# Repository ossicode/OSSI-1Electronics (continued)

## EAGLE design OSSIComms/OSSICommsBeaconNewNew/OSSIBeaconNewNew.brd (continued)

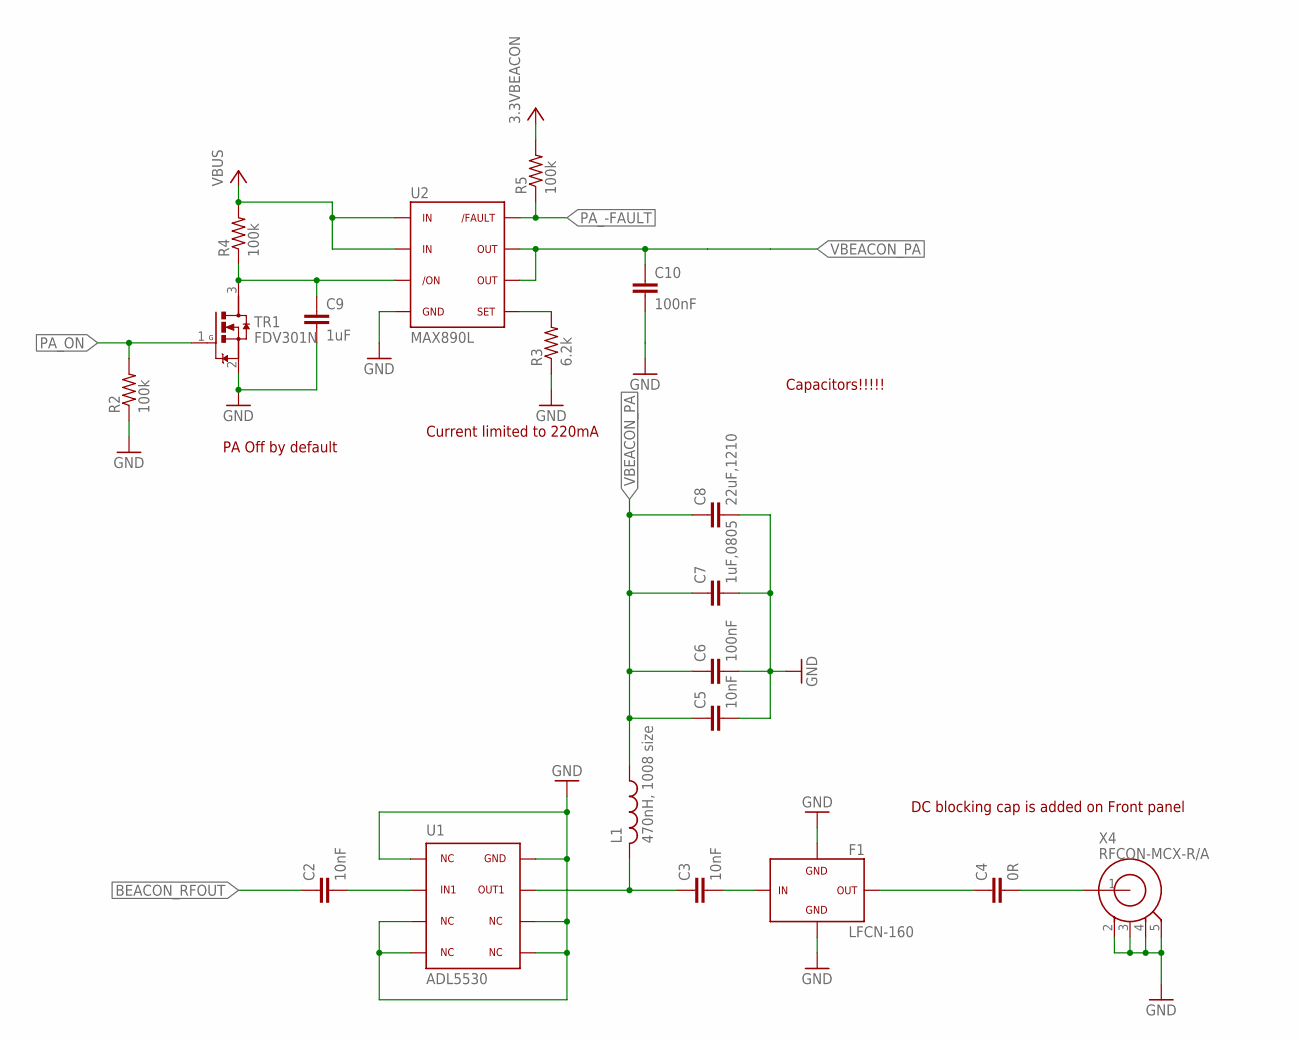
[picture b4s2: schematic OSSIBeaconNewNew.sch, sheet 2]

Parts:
C2, C3, C5: 10nF; C0603(1608)
C4: 0R; C0603(1608)
C6, C10: 100nF; C0603(1608)
C7: 1uF,0805; C0805(2012)
C8: 22uF,1210; C1210-GCM32
C9: 1uF; C0603(1608)
F1: LFCN-160; LFCN
L1: 470nH, 1008 size; L1008(2520)
R2, R4, R5: 100k; R0603(1608)
R3: 6.2k; R0603(1608)
TR1: FDV301N; SOT23
U1: ADL5530; LFCSP8_CP
U2: MAX890L; SO8
X4: RFCON-MCX-R/A; MCX-R/A

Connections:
3.3VBEACON: R5.2; also elsewhere on the board
BEACON_RFOUT: C2.1; also elsewhere on the board
GND: C5.2, C6.2, C7.2, C8.P$2 (2), C9.2, C10.2, F1.2, F1.4, R2.1, R3.1, TR1.2 (S), U1.1, U1.3, U1.4, U1.5, U1.6, U1.8, U2.4, X4.2, X4.3, X4.4, X4.5; also elsewhere on the board
unnamed: C9.1, R4.1, TR1.3 (D), U2.3
unnamed: R3.2, U2.5
unnamed: C2.2, U1.2
unnamed: C3.1, L1.P$2 (2), U1.7
unnamed: C3.2, F1.1
unnamed: C4.1, F1.3
unnamed: C4.2, X4.1
PA_-FAULT: R5.1, U2.8; also elsewhere on the board
PA_ON: R2.2, TR1.1 (G); also elsewhere on the board
VBEACON_PA: C5.1, C6.1, C7.1, C8.P$1 (1), C10.1, L1.P$1 (1), U2.6, U2.7
VBUS: R4.2, U2.1, U2.2; also elsewhere on the board

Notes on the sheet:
Capacitors!!!!!
PA Off by default
Current limited to 220mA
DC blocking cap is added on Front panel

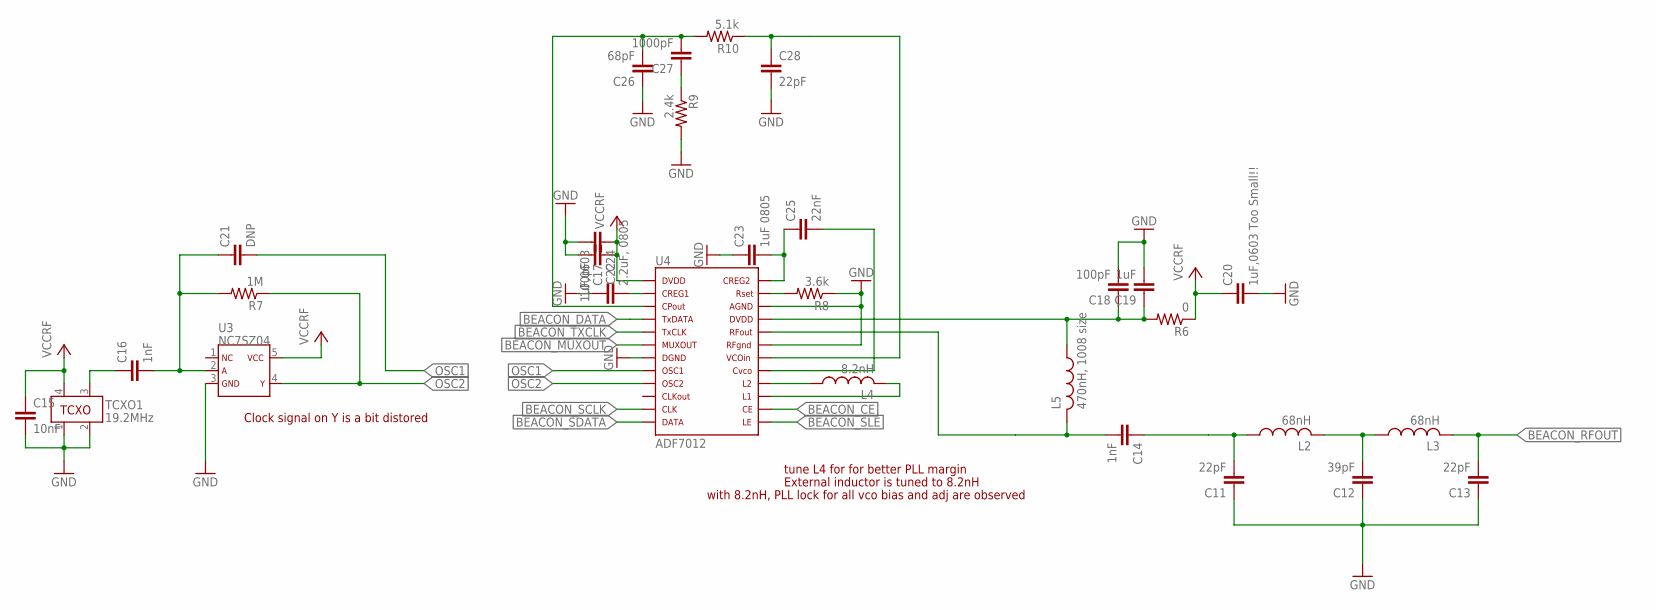
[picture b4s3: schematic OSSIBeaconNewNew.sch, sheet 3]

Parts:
C11, C13, C28: 22pF; C0603(1608)
C12: 39pF; C0603(1608)
C14, C16: 1nF; C0603(1608)
C15: 10nF; C0603(1608)
C17: 2.2uF, 0805; C0805(2012)
C18, C22: 100pF; C0603(1608)
C19: 1uF; C0603(1608)
C20: 1uF,0603 Too Small!!; C0603(1608)
C21: DNP; C0603(1608)
C23: 1uF 0805; C0805(2012)
C24: 1uF,0603; C0603(1608)
C25: 22nF; C0603(1608)
C26: 68pF; C0603(1608)
C27: 1000pF; C0603(1608)
L2, L3: 68nH; L0603(1608)
L4: 8.2nH; L0603(1608)
L5: 470nH, 1008 size; L1008(2520)
R6: 0; R0603(1608)
R7: 1M; R0603(1608)
R8: 3.6k; R0603(1608)
R9: 2.4k; R0603(1608)
R10: 5.1k; R0603(1608)
TCXO1: 19.2MHz; TCXO_M532
U3: NC7SZ04; SC70-5
U4: ADF7012; TSSOP24

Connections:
BEACON_CE: U4.14 (CE); also elsewhere on the board
BEACON_DATA: U4.4 (TXDATA); also elsewhere on the board
BEACON_MUXOUT: U4.6 (MUXOUT); also elsewhere on the board
BEACON_RFOUT: C13.2, L3.2; also elsewhere on the board
BEACON_SCLK: U4.11 (CLK); also elsewhere on the board
BEACON_SDATA: U4.12 (DATA); also elsewhere on the board
BEACON_SLE: U4.13 (LE); also elsewhere on the board
BEACON_TXCLK: U4.5 (TXCLK); also elsewhere on the board
GND: C11.1, C12.1, C13.1, C15.2, C17.1, C18.2, C19.2, C20.2, C22.2, C23.1, C24.2, C26.1, C28.2, R8.1, R9.2, TCXO1.1, TCXO1.2, U3.3, U4.7 (DGND), U4.19 (RFGND), U4.22 (AGND); also elsewhere on the board
unnamed: L4.1, U4.16 (L2)
unnamed: L4.2, U4.15 (L1)
unnamed: C23.2, C25.1, U4.24 (CREG2)
unnamed: C25.2, U4.17 (CVCO)
unnamed: R8.2, U4.23 (RSET)
unnamed: C27.1, R9.1
unnamed: C14.2, L5.P$2 (2), U4.20 (RFOUT)
unnamed: C28.1, R10.1, U4.18 (VCOIN)
unnamed: C17.2, U4.2 (CREG1)
unnamed: C26.2, C27.2, R10.2, U4.3 (CPOUT)
unnamed: C18.1, C19.1, L5.P$1 (1), R6.2, U4.21 (DVDD_2)
unnamed: C11.2, C14.1, L2.1
unnamed: C12.2, L2.2, L3.1
unnamed: C16.2, C21.1, R7.2, U3.2
unnamed: C16.1, TCXO1.3
OSC1: C21.2, U4.8 (OSC1)
OSC2: R7.1, U3.4, U4.9 (OSC2)
VCCRF: C15.1, C20.1, C22.1, C24.1, R6.1, TCXO1.4, U3.5, U4.1 (DVDD_1); also elsewhere on the board

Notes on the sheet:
tune L4 for for better PLL margin
Clock signal on Y is a bit distored
External inductor is tuned to 8.2nH
with 8.2nH, PLL lock for all vco bias and adj are observed

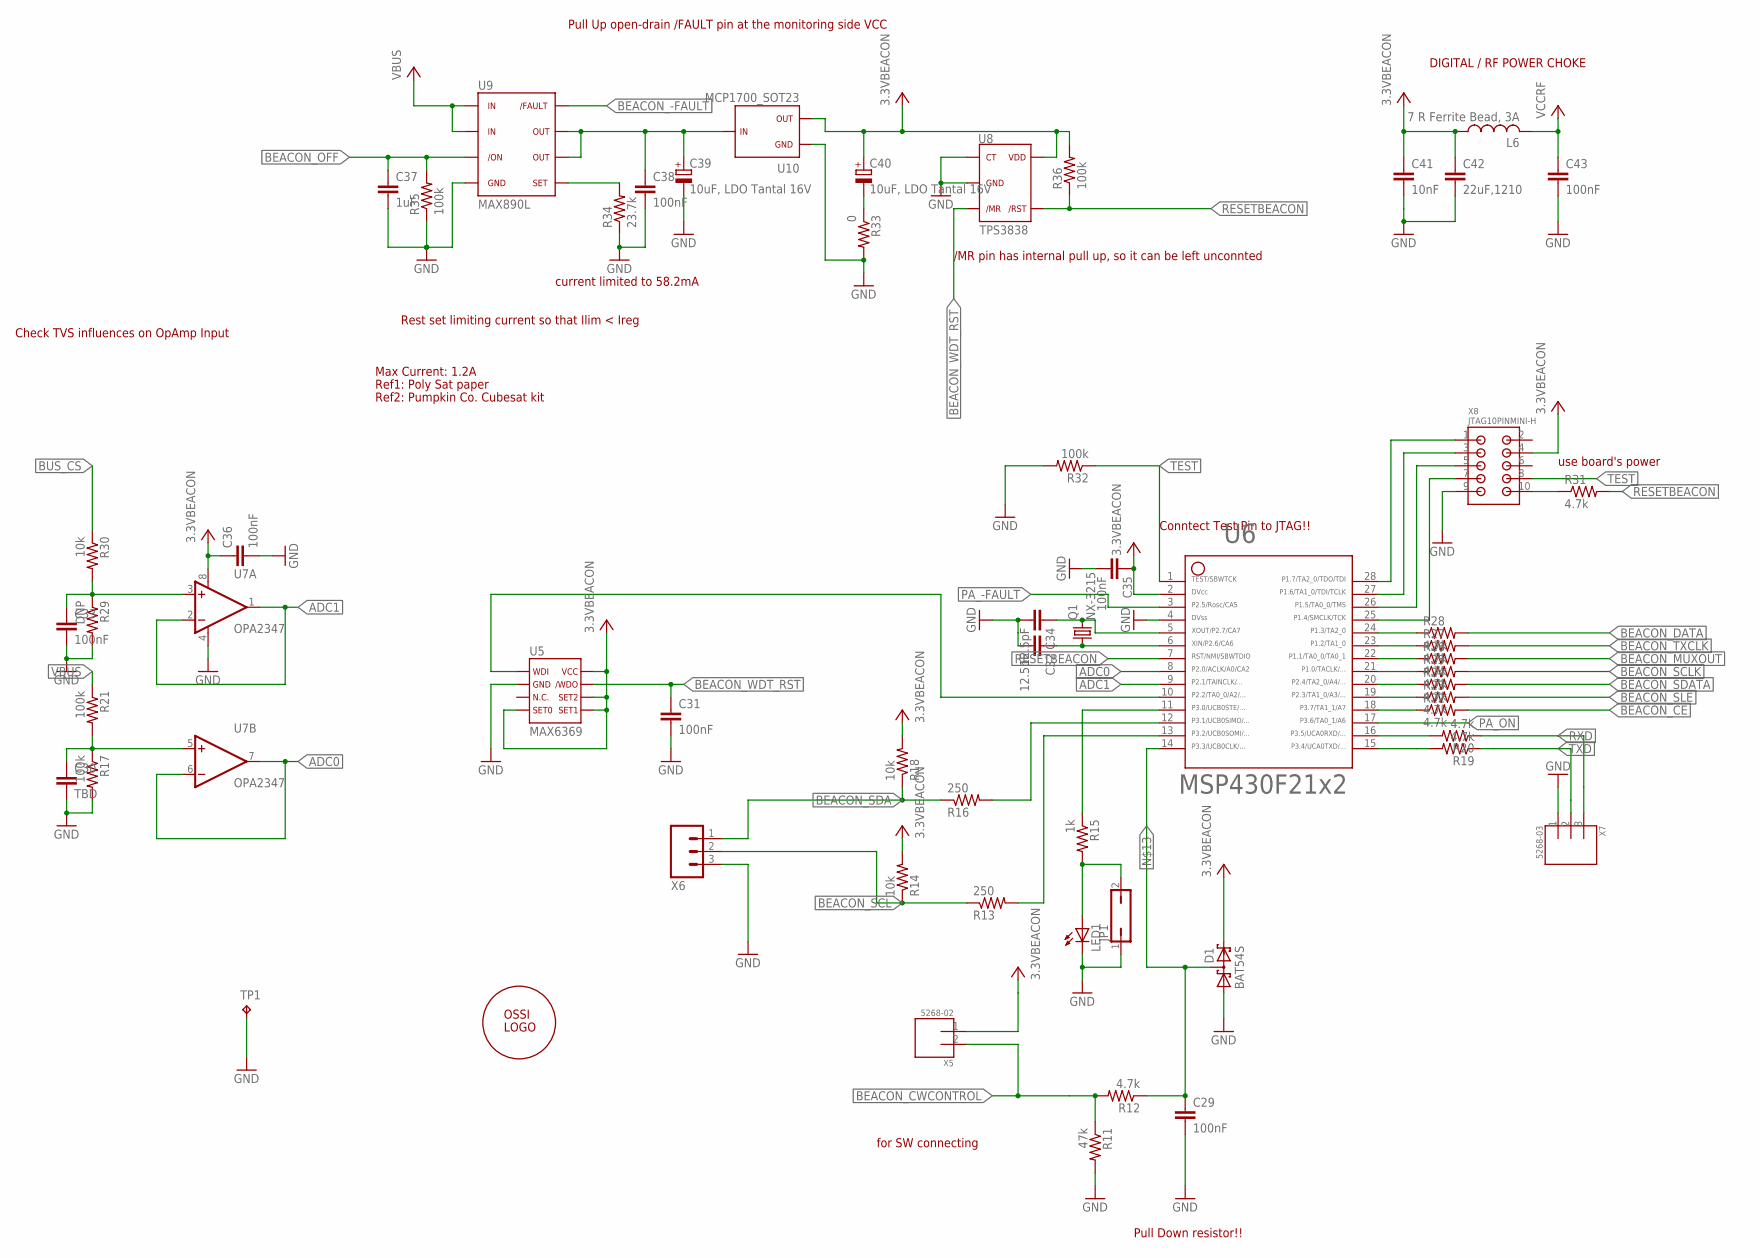
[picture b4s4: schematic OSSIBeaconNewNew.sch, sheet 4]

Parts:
C29, C31, C33, C35, C36, C38, C43: 100nF; C0603(1608)
C30: TBD; C0603(1608)
C32, C34: 12.5pF; C0603(1608)
C37: 1uF; C0603(1608)
C39, C40: 10uF, LDO Tantal 16V; C1206(3216)-A
C41: 10nF; C0603(1608)
C42: 22uF,1210; C1210-GCM32
D1: BAT54S; SOT23
JP1: JP1Q; JP1
L6: 7 R Ferrite Bead, 3A; L0805(2012)
LED1: LED0603; LED-0603
Q1: NX-3215
R11: 47k; R0603(1608)
R12, R19, R20, R22, R23, R24, R25, R26, R27, R28, R31: 4.7k; R0603(1608)
R13, R16: 250; R0603(1608)
R14, R18, R30: 10k; R0603(1608)
R15: 1k; R0603(1608)
R17, R21, R32, R35, R36: 100k; R0603(1608)
R29: DNP; R0603(1608)
R33: 0; R0603(1608)
R34: 23.7k; R0603(1608)
TP1: TP; TP-13
U5: MAX6369; SOT23-8
U6: MSP430F2132; PW28
U7: OPA2347; SOT23-8DCN
U8: TPS3838; SOT23-5DBV
U9: MAX890L; SO8
U10: MCP1700_SOT23; SOT23
U$1: OSSILOGORECT; OSSILOGORECT1005
X5: 5268-02; 5628-02
X6: M03PTH; 1X03
X7: 5268-03
X8: JTAG10PINMINI-H; M50-3200545

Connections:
3.3VBEACON: C35.1, C36.1, C40.1 (+), C41.1, C42.P$1 (1), D1.2 (C2), L6.1, R14.2, R18.2, R36.2, U5.4, U5.5, U5.6, U5.8, U6.2, U7.8 (V+), U8.5, U10.2, X5.1, X8.4; also elsewhere on the board
ADC0: U6.8, U7.6 (-IN), U7.7 (OUT)
ADC1: U6.9, U7.1 (OUT), U7.2 (-IN)
BEACON_-FAULT: U9.8; also elsewhere on the board
BEACON_CE: R22.2; also elsewhere on the board
BEACON_CWCONTROL: R11.1, R12.2, X5.2
BEACON_DATA: R28.2; also elsewhere on the board
BEACON_MUXOUT: R26.2; also elsewhere on the board
BEACON_OFF: C37.1, R35.2, U9.3; also elsewhere on the board
BEACON_SCL: R13.1, R14.1, X6.2; also elsewhere on the board
BEACON_SCLK: R25.2; also elsewhere on the board
BEACON_SDA: R16.1, R18.1, X6.1; also elsewhere on the board
BEACON_SDATA: R24.2; also elsewhere on the board
BEACON_SLE: R23.2; also elsewhere on the board
BEACON_TXCLK: R27.2; also elsewhere on the board
BEACON_WDT_RST: C31.1, U5.7, U8.3
BUS_CS: R30.1; also elsewhere on the board
GND: C29.2, C30.2, C31.2, C32.2, C33.2, C34.2, C35.2, C36.2, C37.2, C38.2, C39.2 (-), C41.2, C42.P$2 (2), C43.2, D1.1 (A1), JP1.1, LED1.C, R11.2, R17.2, R29.2, R32.2, R33.2, R34.1, R35.1, TP1.TP, U5.2, U6.4, U7.4 (V-), U8.1, U8.2, U9.4, U10.1, X6.3, X7.1, X8.9; also elsewhere on the board
unnamed: R15.1, U6.11
unnamed: U6.27, X8.3
unnamed: U6.26, X8.5
unnamed: U6.25, X8.7
unnamed: C34.1, Q1.2, U6.5
unnamed: C32.1, Q1.1, U6.6
unnamed: JP1.2, LED1.A, R15.2
unnamed: U6.28, X8.1
unnamed: R16.2, U6.12
unnamed: R13.2, U6.13
unnamed: R20.2, U6.16
unnamed: U5.1, U6.10
unnamed: C29.1, D1.3 (C1A2), R12.1, U6.14
unnamed: C30.1, R17.1, R21.2, U7.5 (+IN)
unnamed: R31.1, X8.10
unnamed: R34.2, U9.5
unnamed: C33.1, R29.1, R30.2, U7.3 (+IN)
unnamed: R19.2, U6.15
unnamed: C40.2 (-), R33.1
unnamed: R28.1, U6.24
unnamed: R27.1, U6.23
unnamed: R26.1, U6.22
unnamed: R25.1, U6.21
unnamed: R24.1, U6.20
unnamed: R23.1, U6.19
unnamed: R22.1, U6.18
unnamed: C38.1, C39.1 (+), U9.6, U9.7, U10.3
PA_-FAULT: U6.3; also elsewhere on the board
PA_ON: U6.17; also elsewhere on the board
RESETBEACON: R31.2, R36.1, U6.7, U8.4
RXD: R20.1, X7.3
TEST: R32.1, U6.1, X8.8
TXD: R19.1, X7.2
VBUS: R21.1, U9.1, U9.2; also elsewhere on the board
VCCRF: C43.1, L6.2; also elsewhere on the board

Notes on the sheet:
Rest set limiting current so that Ilim < Ireg
Pull Up open-drain /FAULT pin at the monitoring side VCC
Max Current: 1.2A
Ref1: Poly Sat paper
Ref2: Pumpkin Co. Cubesat kit
/MR pin has internal pull up, so it can be left unconnted
use board's power
DIGITAL / RF POWER CHOKE
Pull Down resistor!!
Check TVS influences on OpAmp Input
Conntect Test Pin to JTAG!!
current limited to 58.2mA
for SW connecting

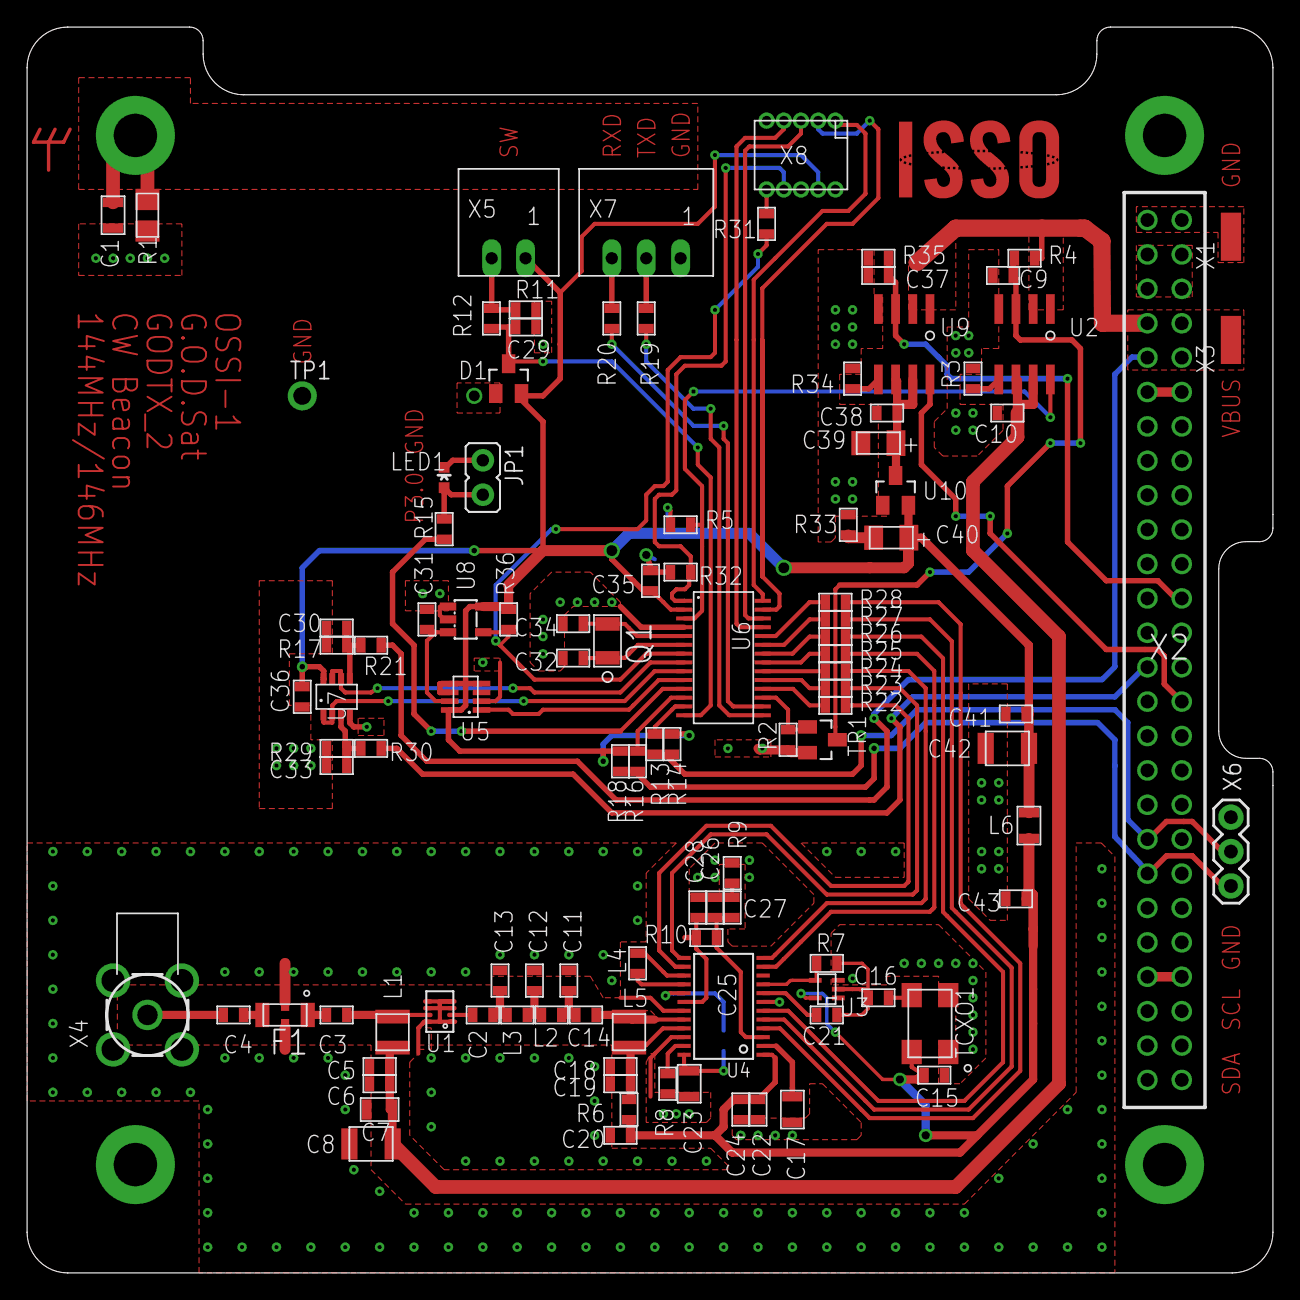
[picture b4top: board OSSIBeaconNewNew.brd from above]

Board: 2 copper layers, 92.0 x 92.0 mm, 116 parts (1 on the bottom side), 83 nets.

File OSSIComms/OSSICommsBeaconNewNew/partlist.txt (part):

Partlist

Exported from OSSIBeaconNewNew.sch at 2013-02-25 ¿ÀÈÄ 3:39:07

EAGLE Version 6.1.0 Copyright (c) 1988-2012 CadSoft

Assembly variant: 

Part     Value                Device             Package        Library  Sheet

C1                            C0805(2012)        C0805(2012)    OSSI     1
C2       10nF                 C0603(1608)        C0603(1608)    OSSI     2
C3       10nF                 C0603(1608)        C0603(1608)    OSSI     2
C4                            C0603(1608)        C0603(1608)    OSSI     2
C5       10nF                 C0603(1608)        C0603(1608)    OSSI     2
C6       100nF                C0603(1608)        C0603(1608)    OSSI     2
C7       1uF,0805             C0805(2012)        C0805(2012)    OSSI     2
C8       22uF,1210            C1210(3225)-GCM32  C1210-GCM32    OSSI     2
C9       1uF                  C0603(1608)        C0603(1608)    OSSI     2
C10      100nF                C0603(1608)        C0603(1608)    OSSI     2
C11      22pF                 C0603(1608)        C0603(1608)    OSSI     3
C12      22pF                 C0603(1608)        C0603(1608)    OSSI     3
C13      22pF                 C0603(1608)        C0603(1608)    OSSI     3
C14      1nF                  C0603(1608)        C0603(1608)    OSSI     3
C15      10nF                 C0603(1608)        C0603(1608)    OSSI     3
C16      1nF                  C0603(1608)        C0603(1608)    OSSI     3
C17      2.2uF, 0805          C0805(2012)        C0805(2012)    OSSI     3
C18      100pF                C0603(1608)        C0603(1608)    OSSI     3
C19      1uF                  C0603(1608)        C0603(1608)    OSSI     3
C20                           C0603(1608)        C0603(1608)    OSSI     3
C21      DNP                  C0603(1608)        C0603(1608)    OSSI     3
C22      100pF                C0603(1608)        C0603(1608)    OSSI     3
C23      1uF 0805             C0805(2012)        C0805(2012)    OSSI     3
C24      1uF,0603             C0603(1608)        C0603(1608)    OSSI     3
C25      22nF                 C0603(1608)        C0603(1608)    OSSI     3
C26      68pF                 C0603(1608)        C0603(1608)    OSSI     3
C27      1000pF               C0603(1608)        C0603(1608)    OSSI     3
C28      22pF                 C0603(1608)        C0603(1608)    OSSI     3
C29      100nF                C0603(1608)        C0603(1608)    OSSI     4
C30      TBD                  C0603(1608)        C0603(1608)    OSSI     4
C31      100nF                C0603(1608)        C0603(1608)    OSSI     4
C32      12.5pF               C0603(1608)        C0603(1608)    OSSI     4
C33      TBD                  C0603(1608)        C0603(1608)    OSSI     4
C34      12.5pF               C0603(1608)        C0603(1608)    OSSI     4
C35      100nF                C0603(1608)        C0603(1608)    OSSI     4
C36      100nF                C0603(1608)        C0603(1608)    OSSI     4
C37      1uF                  C0603(1608)        C0603(1608)    OSSI     4
C38      100nF                C0603(1608)        C0603(1608)    OSSI     4
C39      10uF, LDO Tantal 16V C-TANTAL-A         C1206(3216)-A  OSSI     4
C40      10uF, LDO Tantal 16V C-TANTAL-A         C1206(3216)-A  OSSI     4
C41      10nF                 C0603(1608)        C0603(1608)    OSSI     4
C42      22uF,1210            C1210(3225)-GCM32  C1210-GCM32    OSSI     4
C43      100nF                C0603(1608)        C0603(1608)    OSSI     4
D1       BAT54S               BAT54S             SOT23          OSSI     4
F1       LFCN-160             LFCN-160           LFCN           OSSI     2
H1       MOUNT-PAD-ROUND3.2   MOUNT-PAD-ROUND3.2 3.2-PAD-ROUND  OSSI     1
H2       MOUNT-PAD-ROUND3.2   MOUNT-PAD-ROUND3.2 3.2-PAD-ROUND  OSSI     1
H3       MOUNT-PAD-ROUND3.2   MOUNT-PAD-ROUND3.2 3.2-PAD-ROUND  OSSI     1
H4       MOUNT-PAD-ROUND3.2   MOUNT-PAD-ROUND3.2 3.2-PAD-ROUND  OSSI     1
JP1                           JP1Q               JP1            OSSI     4
L1       470nH, 1008 size     L1008(2502)        L1008(2520)    OSSI     2
L2       68nH                 L0603(1608)        L0603(1608)    OSSI     3
L3       68nH                 L0603(1608)        L0603(1608)    OSSI     3
L4       10nH                 L0603(1608)        L0603(1608)    OSSI     3
L5       470nH, 1008 size     L1008(2502)        L1008(2520)    OSSI     3
L6       5~15R ferrite bead   L0805(2012)        L0805(2012)    OSSI     4
LED1                          LED0603            LED-0603       SparkFun 4
Q1       NX-3215              NX-3215            NX-3215        OSSI     4
R1       511                  RWSL1206           WSL1206        OSSI     1
R2       100k                 R0603(1608)        R0603(1608)    OSSI     2
R3       6.2k                 R0603(1608)        R0603(1608)    OSSI     2
R4       100k                 R0603(1608)        R0603(1608)    OSSI     2
R5       100k                 R0603(1608)        R0603(1608)    OSSI     2
R6       0                    R0603(1608)        R0603(1608)    OSSI     3
R7       1M                   R0603(1608)        R0603(1608)    OSSI     3
R8       3.6k                 R0603(1608)        R0603(1608)    OSSI     3
R9       2.4k                 R0603(1608)        R0603(1608)    OSSI     3
R10      5.1k                 R0603(1608)        R0603(1608)    OSSI     3
R11      47k                  R0603(1608)        R0603(1608)    OSSI     4
R12      4.7k                 R0603(1608)        R0603(1608)    OSSI     4
R13      250                  R0603(1608)        R0603(1608)    OSSI     4
R14      10k                  R0603(1608)        R0603(1608)    OSSI     4
R15      1k                   R0603(1608)        R0603(1608)    OSSI     4
R16      250                  R0603(1608)        R0603(1608)    OSSI     4
R17      100k                 R0603(1608)        R0603(1608)    OSSI     4
R18      10k                  R0603(1608)        R0603(1608)    OSSI     4
R19      4.7k                 R0603(1608)        R0603(1608)    OSSI     4
R20      4.7k                 R0603(1608)        R0603(1608)    OSSI     4
R21      100k                 R0603(1608)        R0603(1608)    OSSI     4
R22      4.7k                 R0603(1608)        R0603(1608)    OSSI     4
R23      4.7k                 R0603(1608)        R0603(1608)    OSSI     4
R24      4.7k                 R0603(1608)        R0603(1608)    OSSI     4
R25      4.7k                 R0603(1608)        R0603(1608)    OSSI     4
R26      4.7k                 R0603(1608)        R0603(1608)    OSSI     4
R27      4.7k                 R0603(1608)        R0603(1608)    OSSI     4
R28      4.7k                 R0603(1608)        R0603(1608)    OSSI     4
R29      100k                 R0603(1608)        R0603(1608)    OSSI     4
R30      100k                 R0603(1608)        R0603(1608)    OSSI     4
R31      4.7k                 R0603(1608)        R0603(1608)    OSSI     4
R32      4.7k                 R0603(1608)        R0603(1608)    OSSI     4
R33      0                    R0603(1608)        R0603(1608)    OSSI     4
R34      23.7k                R0603(1608)        R0603(1608)    OSSI     4
R35      100k                 R0603(1608)        R0603(1608)    OSSI     4
R36      100k                 R0603(1608)        R0603(1608)    OSSI     4
TCXO1    19.2MHz              TCXO-M532          TCXO_M532      OSSI     3
TP1      TP                   TP                 TP-13          OSSI     4
TR1      FDV301N              FDV301N            SOT23          OSSI     2
U1       ADL5530              ADL5530            LFCSP8_CP      OSSI     2
U2       MAX890L              MAX890L            SO8            OSSI     2
U3       NC7SZ04              NC7SZ04            SC70-5         OSSI     3
U4       ADF7012              ADF7012            TSSOP24        OSSI     3
U5       MAX6369              MAX6369            SOT23-8        OSSI     4
U6       MSP430F2132          MSP430F2132        PW28           OSSI     4
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
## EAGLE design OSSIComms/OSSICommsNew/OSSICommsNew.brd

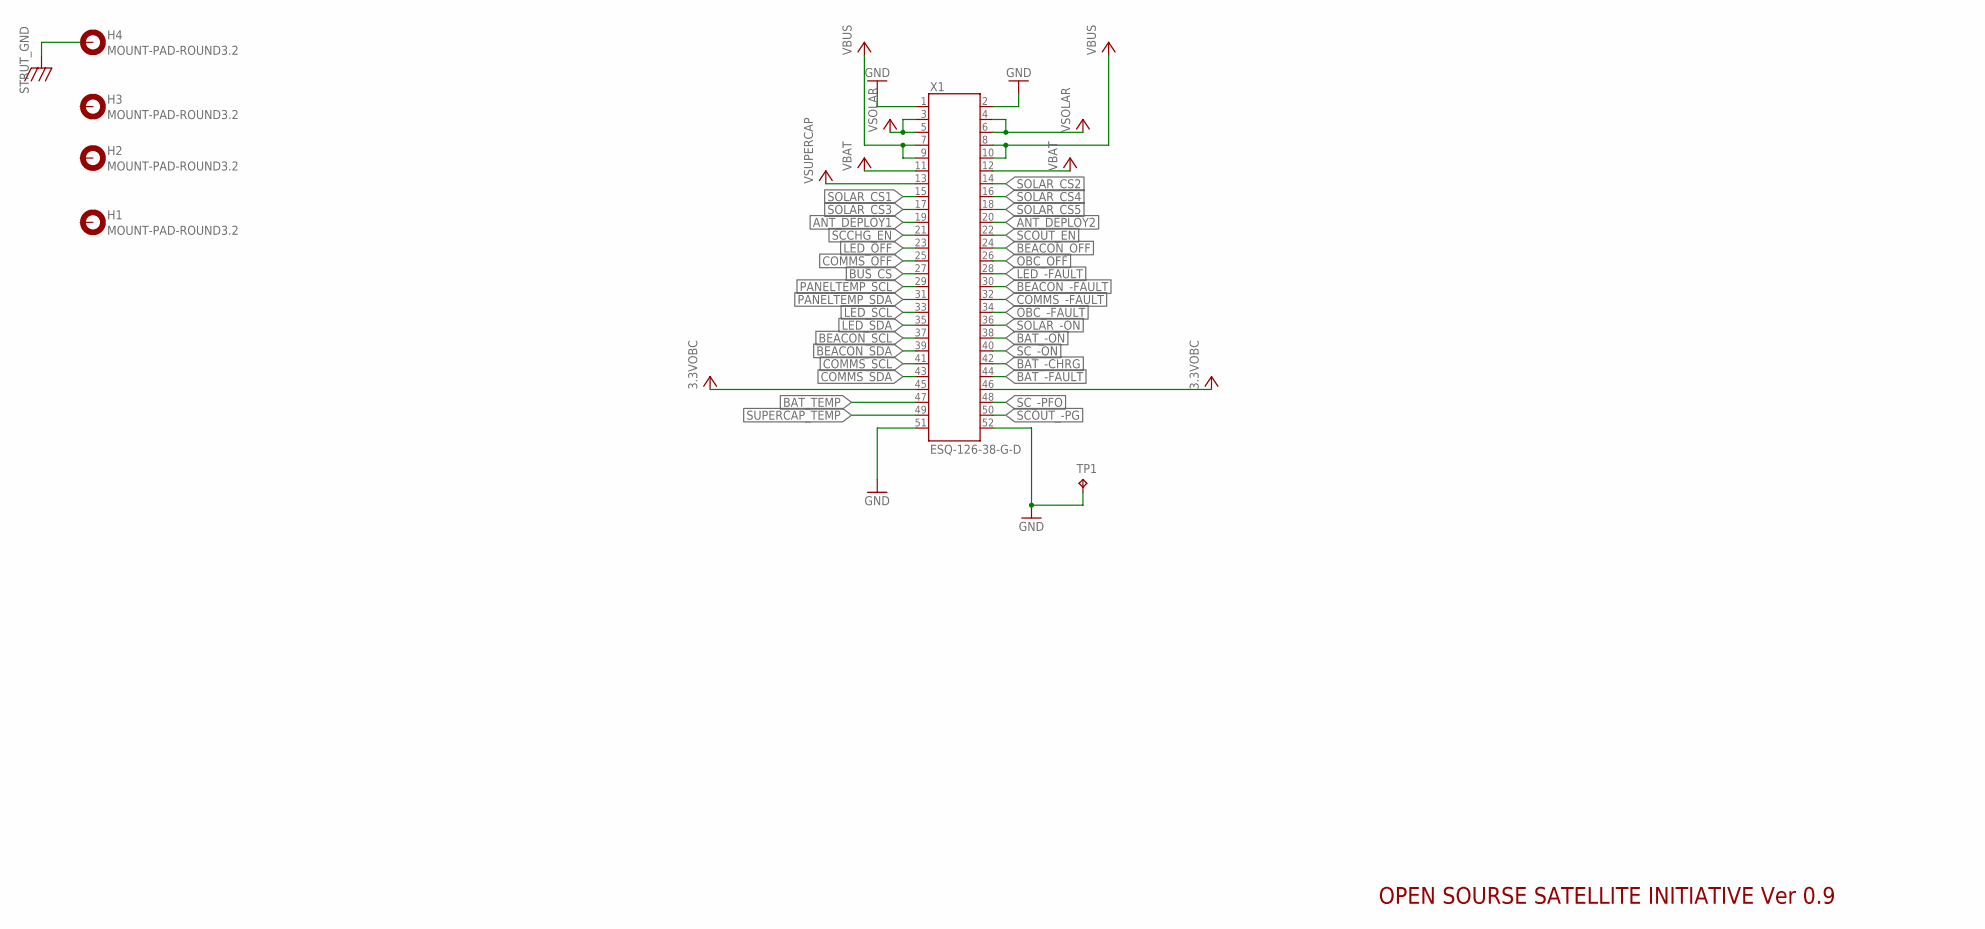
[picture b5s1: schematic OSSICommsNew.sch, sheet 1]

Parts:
H1, H2, H3, H4: MOUNT-PAD-ROUND3.2; 3.2-PAD-ROUND
TP1: TP; TP-13
X1: ESQ-126-38-G-D; ESQ-126-XX-X-D

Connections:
3.3VOBC: X1.45, X1.46
ANT_DEPLOY1: X1.19
ANT_DEPLOY2: X1.20
BAT_-CHRG: X1.42
BAT_-FAULT: X1.44
BAT_-ON: X1.38
BAT_TEMP: X1.47
BEACON_-FAULT: X1.30
BEACON_OFF: X1.24
BEACON_SCL: X1.37
BEACON_SDA: X1.39
BUS_CS: X1.27
COMMS_-FAULT: X1.32; also elsewhere on the board
COMMS_OFF: X1.25; also elsewhere on the board
COMMS_SCL: X1.41; also elsewhere on the board
COMMS_SDA: X1.43; also elsewhere on the board
GND: TP1.TP, X1.1, X1.2, X1.51, X1.52; also elsewhere on the board
LED_-FAULT: X1.28
LED_OFF: X1.23
LED_SCL: X1.33
LED_SDA: X1.35
OBC_-FAULT: X1.34; also elsewhere on the board
OBC_OFF: X1.26; also elsewhere on the board
PANELTEMP_SCL: X1.29
PANELTEMP_SDA: X1.31
SCCHG_EN: X1.21
SCOUT_-PG: X1.50
SCOUT_EN: X1.22
SC_-ON: X1.40
SC_-PFO: X1.48
SOLAR_-ON: X1.36
SOLAR_CS1: X1.15
SOLAR_CS2: X1.14
SOLAR_CS3: X1.17
SOLAR_CS4: X1.16
SOLAR_CS5: X1.18
STRUT_GND: H4.B3,2
SUPERCAP_TEMP: X1.49
VBAT: X1.11, X1.12
VBUS: X1.7, X1.8, X1.9, X1.10; also elsewhere on the board
VSOLAR: X1.3, X1.4, X1.5, X1.6
VSUPERCAP: X1.13

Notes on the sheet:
OPEN SOURSE SATELLITE INITIATIVE Ver 0.9
